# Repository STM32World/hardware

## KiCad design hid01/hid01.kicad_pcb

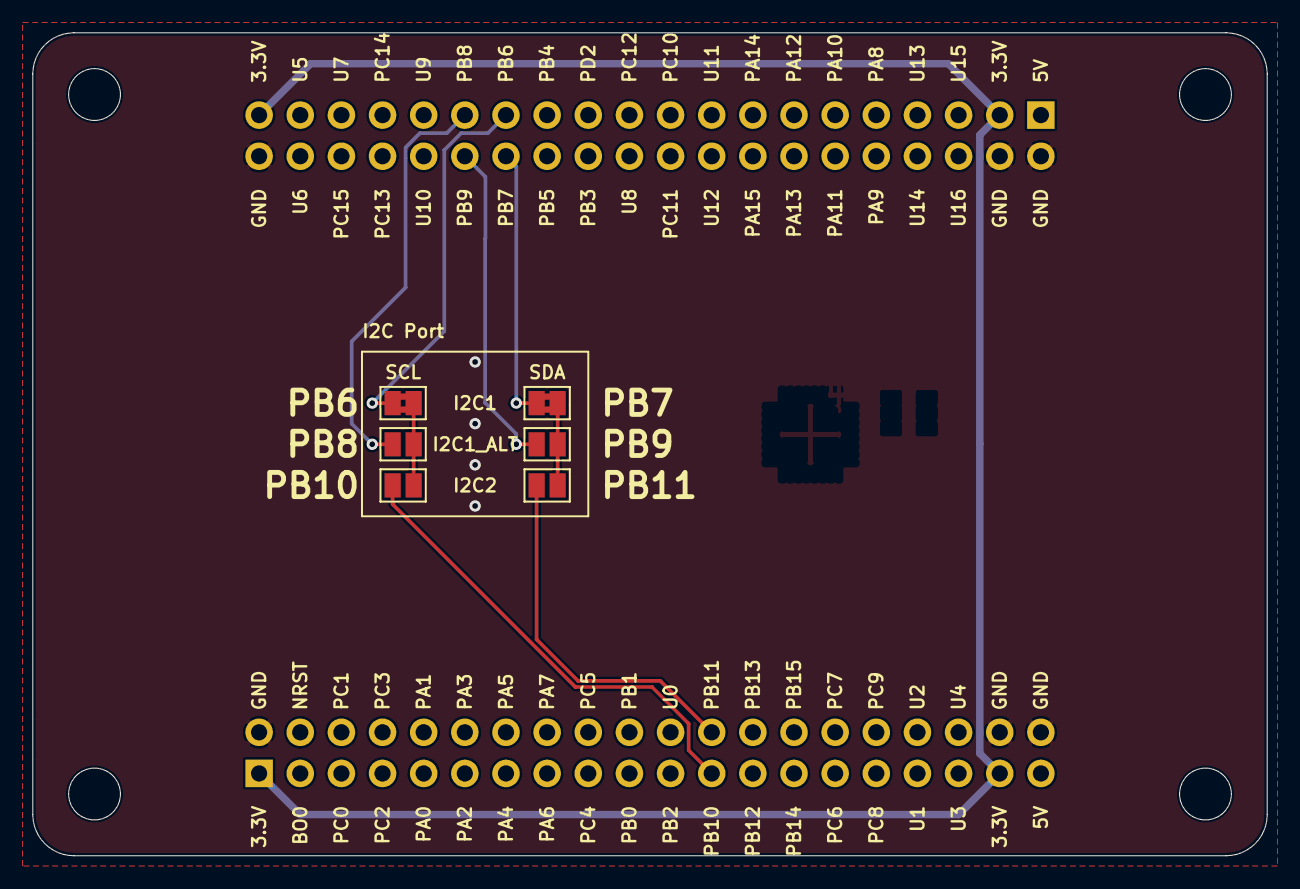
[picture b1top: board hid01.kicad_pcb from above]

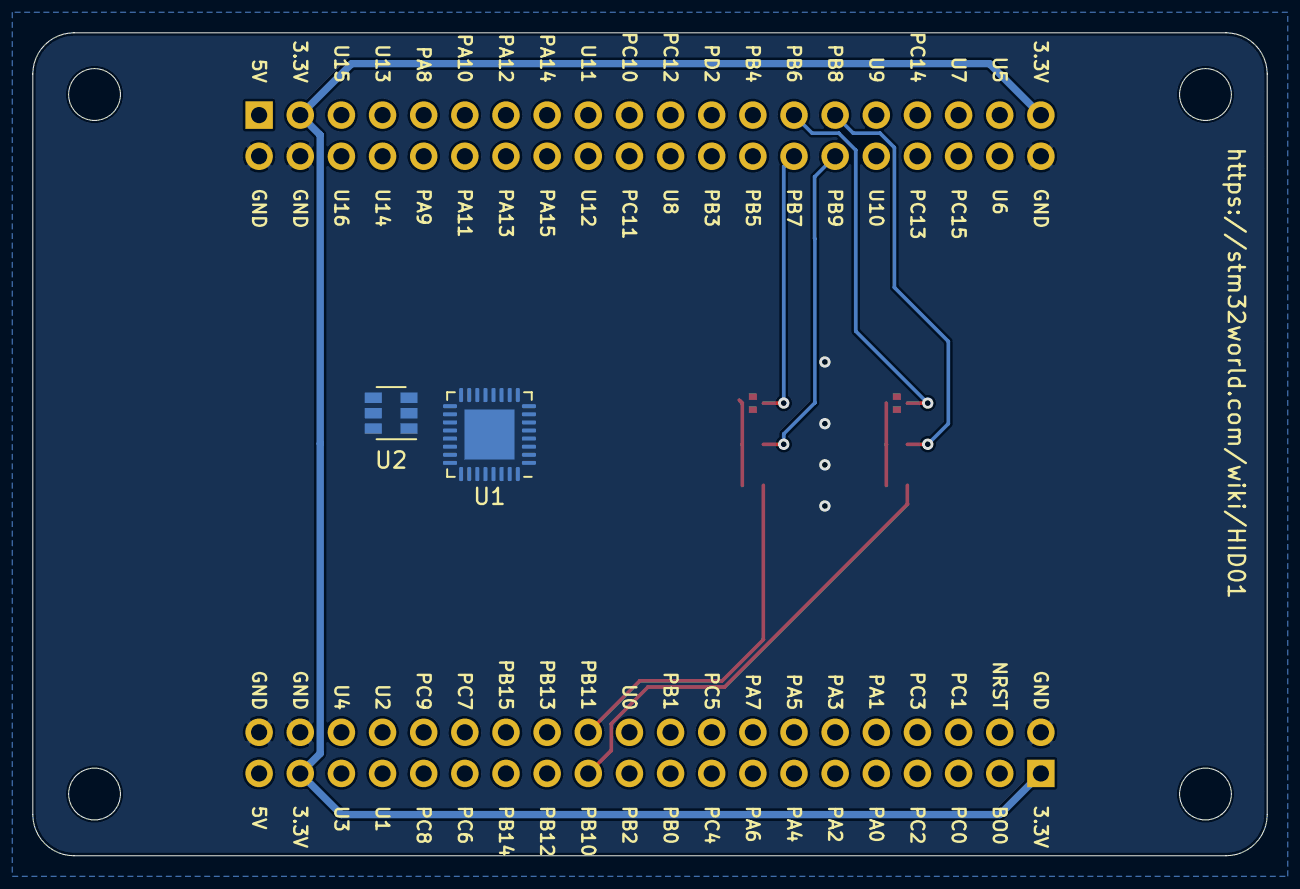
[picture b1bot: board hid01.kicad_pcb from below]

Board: 2 copper layers, 76.2 x 50.8 mm, 9 parts (2 on the bottom side), 10 nets.

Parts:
J1: STM32WORLD_BASE
JP1, JP3: SolderJumper-2_P1.3mm_Bridged2Bar_Pad1.0x1.5mm
JP2, JP4, JP7, JP8: SolderJumper-2_P1.3mm_Open_Pad1.0x1.5mm
U1: TCA6424ARGJR; QFN-32-1EP_5x5mm_P0.5mm_EP3.1x3.1mm
U2: TTP223E-HA6; SOT-23-6

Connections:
+3V3: J1.1, J1.37, J1.43, J1.79, U1.27, U1.28, U1.31
GND: J1.2, J1.38, J1.40, J1.42, J1.44, J1.80, U1.25, U1.26, U1.33
I2C1_SCL: J1.67, JP1.1
I2C1_SCL_ALT: J1.69, JP2.1
I2C1_SDA: J1.68, JP3.1
I2C1_SDA_ALT: J1.70, JP4.1
I2C2_SCL: J1.23, JP7.1
I2C2_SDA: J1.24, JP8.1
SCL: JP1.2, JP2.2, JP7.2, U1.29
SDA: JP3.2, JP4.2, JP8.2, U1.30

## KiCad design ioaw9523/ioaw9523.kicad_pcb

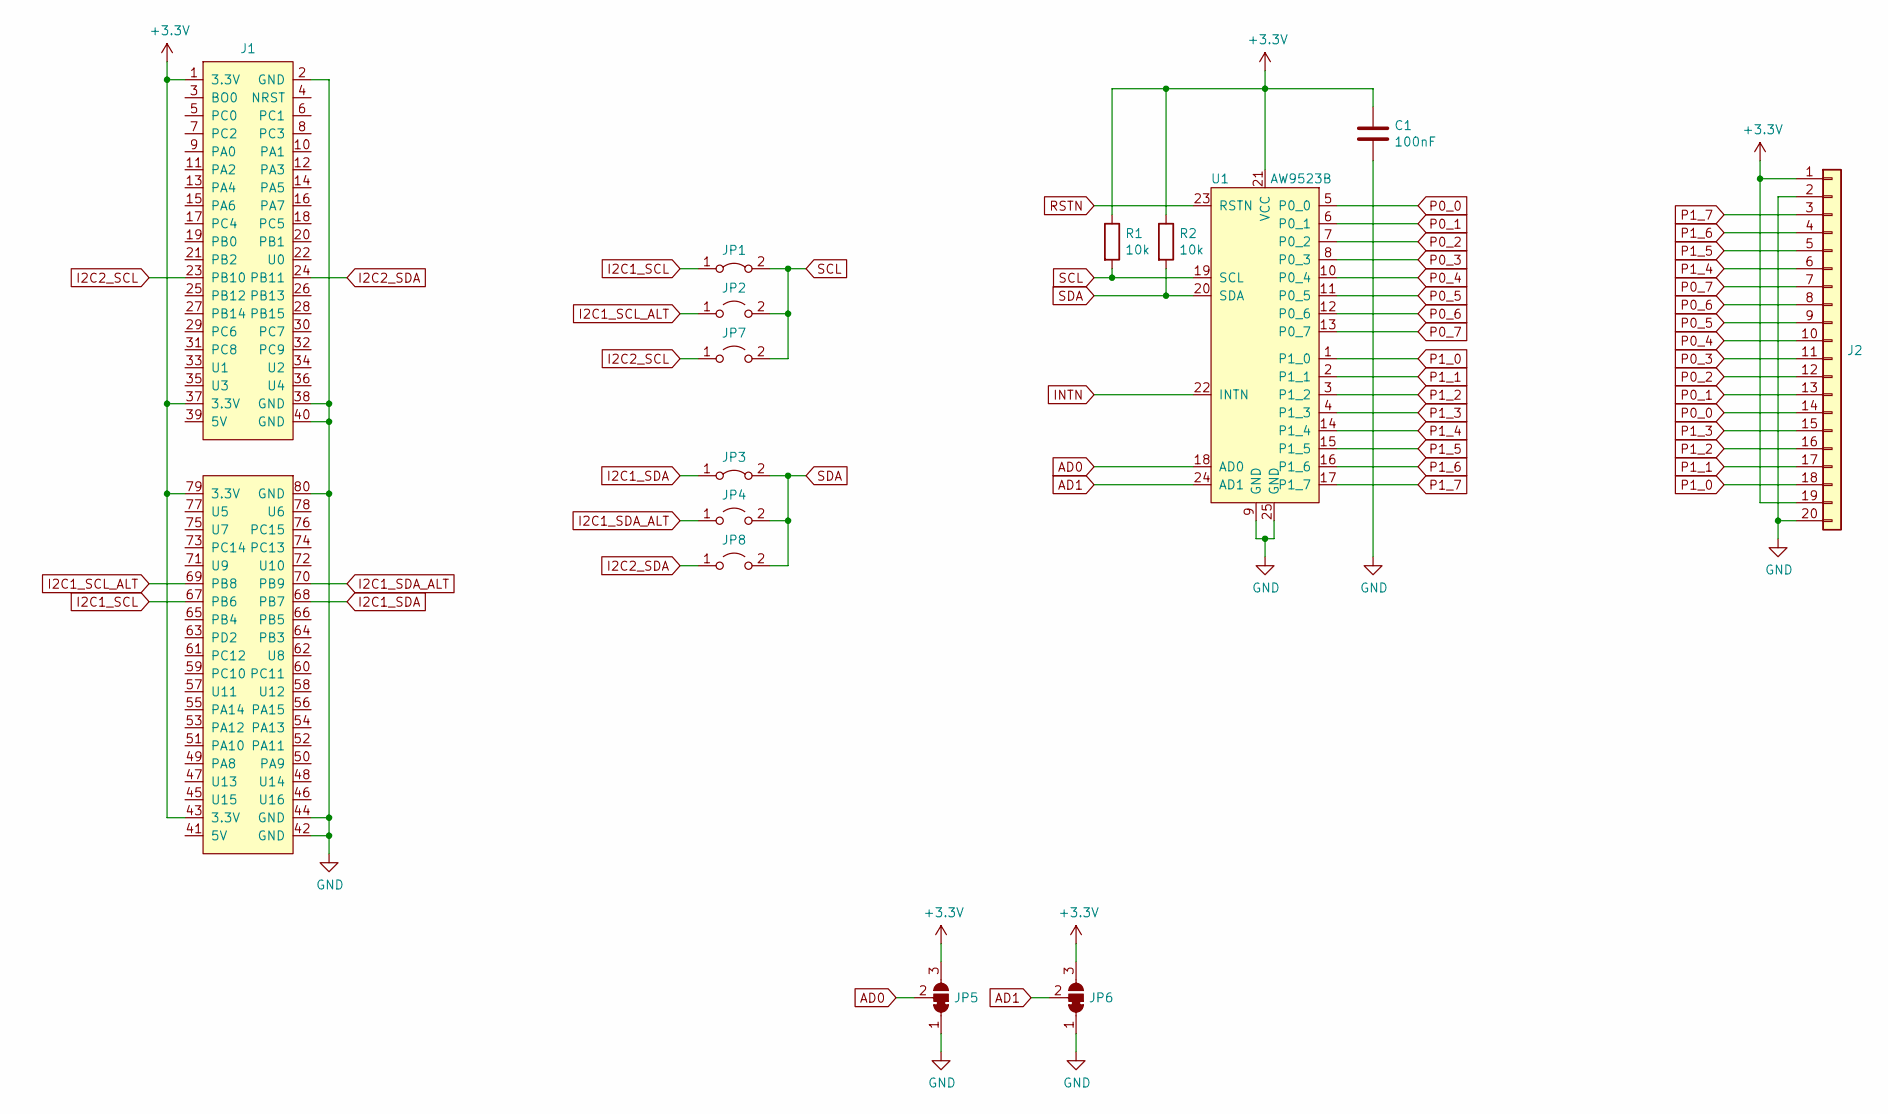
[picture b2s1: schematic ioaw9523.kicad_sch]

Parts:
C1: C_100NF_0603; C_0603_1608Metric; LCSC C14663
J1: STM32WORLD_BASE
J2: PinHeader_2x10_P2.54mm_Horizontal
JP1, JP3: SolderJumper-2_P1.3mm_Bridged2Bar_Pad1.0x1.5mm
JP2, JP4, JP7, JP8: SolderJumper-2_P1.3mm_Open_Pad1.0x1.5mm
JP5, JP6: SolderJumper-3_P1.3mm_Bridged12_Pad1.0x1.5mm
R1, R2: R_10K_0603; R_0603_1608Metric; LCSC C25804
U1: AW9523B; TQFN-24-1EP_4x4mm_P0.5mm_EP2.8x2.8mm_PullBack; LCSC C148077

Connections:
+3V3: C1.1, J1.1 (3.3V), J1.37 (3.3V), J1.43 (3.3V), J1.79 (3.3V), J2.1, J2.19, JP5.3 (B), JP6.3 (B), R1.1, R2.1, U1.21 (VCC)
AD0: JP5.2 (C), U1.18 (AD0)
AD1: JP6.2 (C), U1.24 (AD1)
GND: C1.2, J1.2 (GND), J1.38 (GND), J1.40 (GND), J1.42 (GND), J1.44 (GND), J1.80 (GND), J2.2, J2.20, JP5.1 (A), JP6.1 (A), U1.9 (GND), U1.25 (GND)
I2C1_SCL: J1.67 (PB6), JP1.1 (A)
I2C1_SCL_ALT: J1.69 (PB8), JP2.1 (A)
I2C1_SDA: J1.68 (PB7), JP3.1 (A)
I2C1_SDA_ALT: J1.70 (PB9), JP4.1 (A)
I2C2_SCL: J1.23 (PB10), JP7.1 (A)
I2C2_SDA: J1.24 (PB11), JP8.1 (A)
INTN: U1.22 (INTN)
P0_0: J2.14, U1.5 (P0_0)
P0_1: J2.13, U1.6 (P0_1)
P0_2: J2.12, U1.7 (P0_2)
P0_3: J2.11, U1.8 (P0_3)
P0_4: J2.10, U1.10 (P0_4)
P0_5: J2.9, U1.11 (P0_5)
P0_6: J2.8, U1.12 (P0_6)
P0_7: J2.7, U1.13 (P0_7)
P1_0: J2.18, U1.1 (P1_0)
P1_1: J2.17, U1.2 (P1_1)
P1_2: J2.16, U1.3 (P1_2)
P1_3: J2.15, U1.4 (P1_3)
P1_4: J2.6, U1.14 (P1_4)
P1_5: J2.5, U1.15 (P1_5)
P1_6: J2.4, U1.16 (P1_6)
P1_7: J2.3, U1.17 (P1_7)
RSTN: U1.23 (RSTN)
SCL: JP1.2 (B), JP2.2 (B), JP7.2 (B), R1.2, U1.19 (SCL)
SDA: JP3.2 (B), JP4.2 (B), JP8.2 (B), R2.2, U1.20 (SDA)

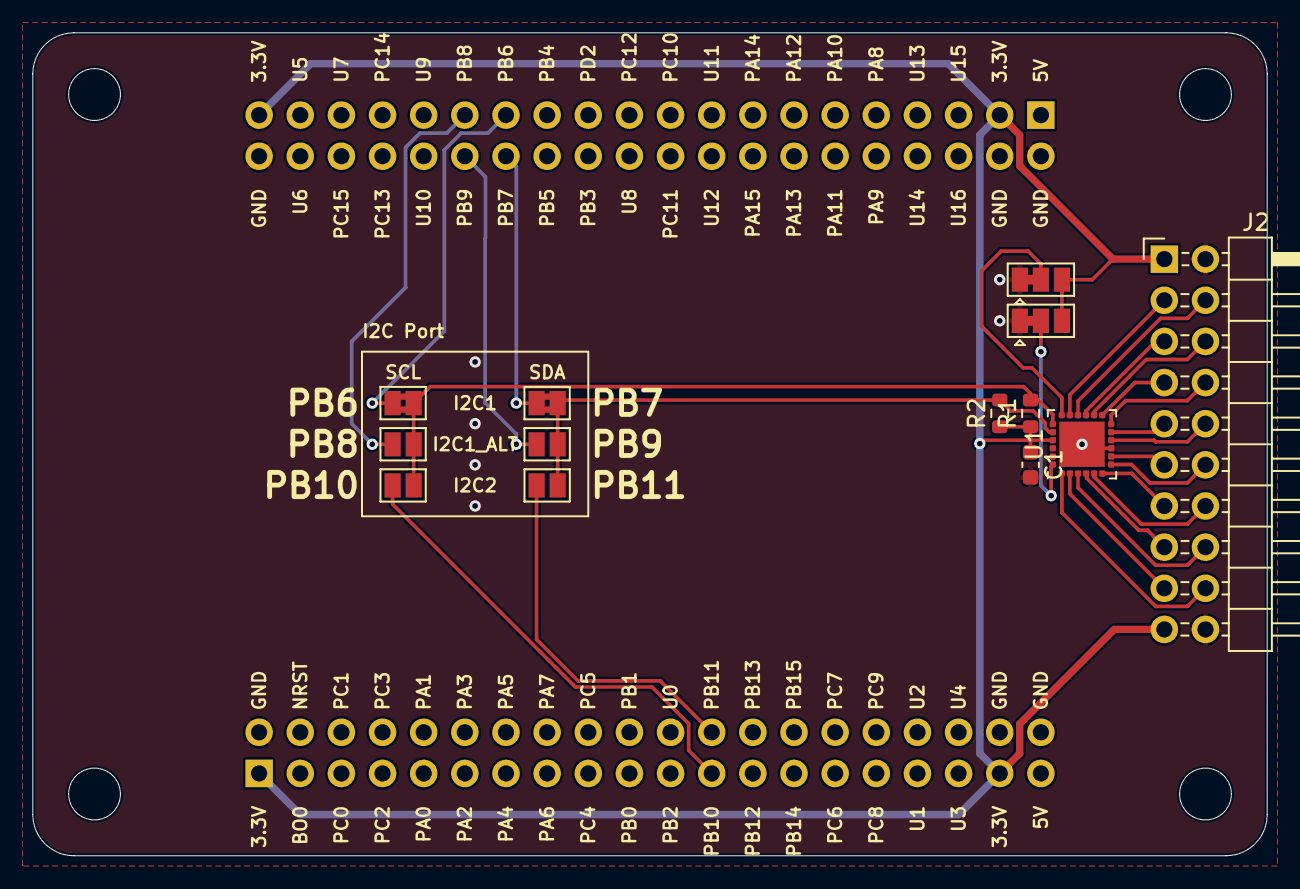
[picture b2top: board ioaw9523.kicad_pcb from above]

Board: 2 copper layers, 76.2 x 50.8 mm, 14 parts (0 on the bottom side), 28 nets.

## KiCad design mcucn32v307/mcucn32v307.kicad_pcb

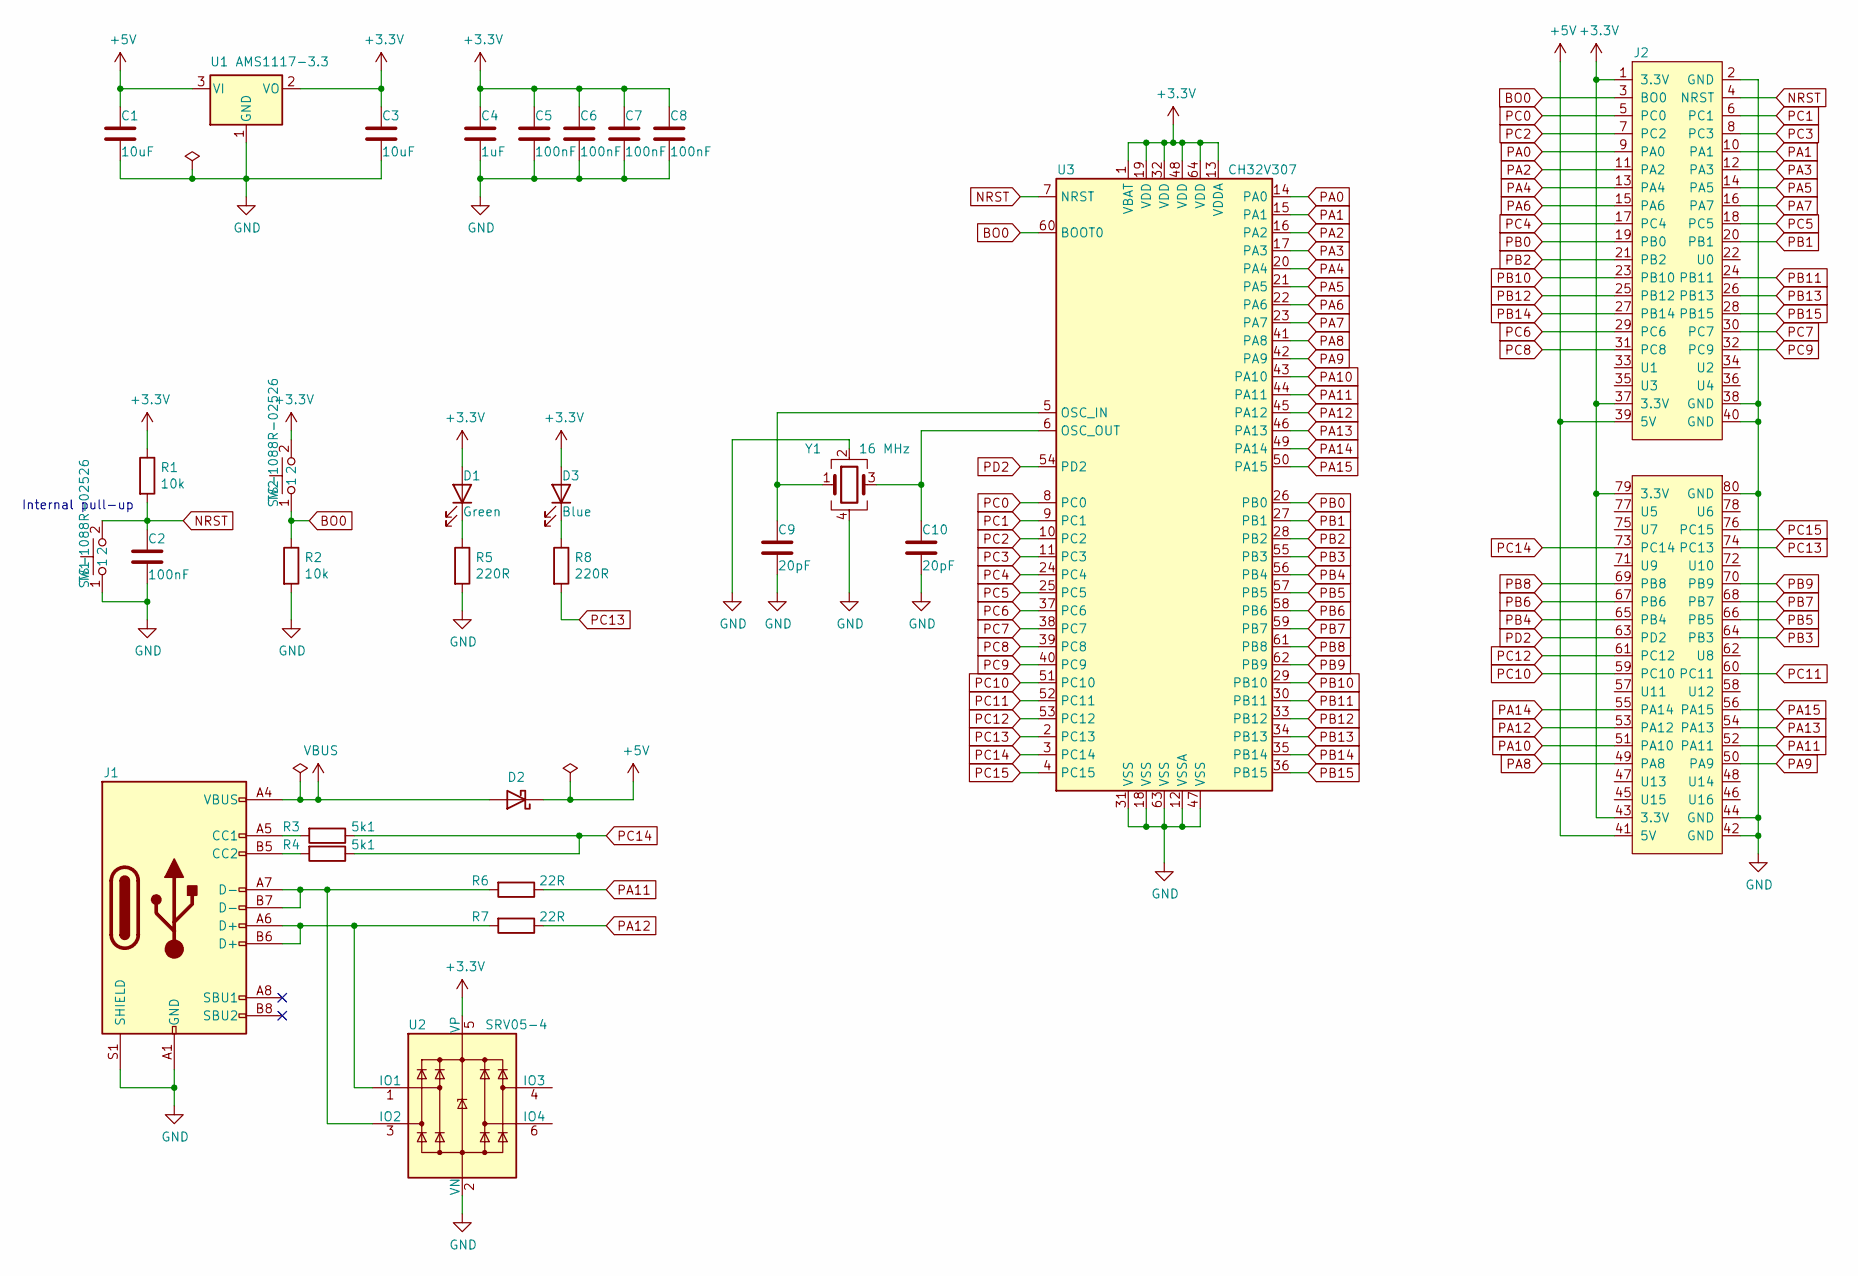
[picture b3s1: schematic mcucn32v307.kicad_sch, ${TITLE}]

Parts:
C1, C3: C_10UF_0805; C_0805_2012Metric; LCSC C15850
C2, C5, C6, C7, C8: C_100NF_0603; C_0603_1608Metric; LCSC C14663
C4: C_1UF_0603; C_0603_1608Metric; LCSC C15849
C9, C10: C_20PF_0603; C_0603_1608Metric; LCSC C1648
D1: LED_GREEN_0603; LED_0603_1608Metric; LCSC C72043
D2: LCSC C8598
D3: LED_BLUE_0603; LED_0603_1608Metric; LCSC C72041
J1: USB_C_Receptacle_USB2.0; USB_C_Receptacle_HRO_TYPE-C-31-M-12; LCSC C165948
J2: STM32WORLD_BASE
R1, R2: R_10K_0603; R_0603_1608Metric; LCSC C25804
R3, R4: R_5.1K_0603; R_0603_1608Metric; LCSC C23186
R5, R8: R_220_0603; R_0603_1608Metric; LCSC C22962
R6, R7: R_22_0603; R_0603_1608Metric; LCSC C23345
SW1, SW2: TS-1088R-02526; LCSC C455281
U1: AMS1117-3.3; SOT-223-3_TabPin2; LCSC C6186
U2: SRV05-4; SOT-23-6; LCSC C85364
U3: CH32V307; LQFP-64_10x10mm_P0.5mm; LCSC C2988083
Y1: X_16MHZ; Crystal_SMD_3225-4Pin_3.2x2.5mm; LCSC C13738

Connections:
+3V3: C3.1, C4.1, C5.1, C6.1, C7.1, C8.1, D1.2 (A), D3.2 (A), J2.1 (3.3V), J2.37 (3.3V), J2.43 (3.3V), J2.79 (3.3V), R1.1, SW2.2, U1.2 (VO), U2.5 (VP), U3.1 (VBAT), U3.13 (VDDA), U3.19 (VDD), U3.32 (VDD), U3.48 (VDD), U3.64 (VDD)
+5V: C1.1, D2.1 (K), J2.39 (5V), J2.41 (5V), U1.3 (VI)
BO0: J2.3 (BO0), R2.1, SW2.1, U3.60 (BOOT0)
GND: C1.2, C2.2, C3.2, C4.2, C5.2, C6.2, C7.2, C8.2, C9.2, C10.2, J1.A1 (GND), J1.A12 (GND), J1.B1 (GND), J1.B12 (GND), J1.S1 (SHIELD), J2.2 (GND), J2.38 (GND), J2.40 (GND), J2.42 (GND), J2.44 (GND), J2.80 (GND), R2.2, R5.2, SW1.1, U1.1 (GND), U2.2 (VN), U3.12 (VSSA), U3.18 (VSS), U3.31 (VSS), U3.47 (VSS), U3.63 (VSS), Y1.2, Y1.4
NRST: C2.1, J2.4 (NRST), R1.2, SW1.2, U3.7 (NRST)
unnamed: C9.1, U3.5 (OSC_IN), Y1.1
unnamed: C10.1, U3.6 (OSC_OUT), Y1.3
unnamed: D1.1 (K), R5.1
unnamed: D3.1 (K), R8.1
unnamed: J1.A5 (CC1), R3.2
unnamed: J1.A6 (D+), J1.B6 (D+), R7.2, U2.1 (IO1)
unnamed: J1.A7 (D-), J1.B7 (D-), R6.2, U2.3 (IO2)
unnamed: J1.B5 (CC2), R4.2
PA0: J2.9 (PA0), U3.14 (PA0)
PA1: J2.10 (PA1), U3.15 (PA1)
PA2: J2.11 (PA2), U3.16 (PA2)
PA3: J2.12 (PA3), U3.17 (PA3)
PA4: J2.13 (PA4), U3.20 (PA4)
PA5: J2.14 (PA5), U3.21 (PA5)
PA6: J2.15 (PA6), U3.22 (PA6)
PA7: J2.16 (PA7), U3.23 (PA7)
PA8: J2.49 (PA8), U3.41 (PA8)
PA9: J2.50 (PA9), U3.42 (PA9)
PA10: J2.51 (PA10), U3.43 (PA10)
PA11: J2.52 (PA11), R6.1, U3.44 (PA11)
PA12: J2.53 (PA12), R7.1, U3.45 (PA12)
PA13: J2.54 (PA13), U3.46 (PA13)
PA14: J2.55 (PA14), U3.49 (PA14)
PA15: J2.56 (PA15), U3.50 (PA15)
PB0: J2.19 (PB0), U3.26 (PB0)
PB1: J2.20 (PB1), U3.27 (PB1)
PB2: J2.21 (PB2), U3.28 (PB2)
PB3: J2.64 (PB3), U3.55 (PB3)
PB4: J2.65 (PB4), U3.56 (PB4)
PB5: J2.66 (PB5), U3.57 (PB5)
PB6: J2.67 (PB6), U3.58 (PB6)
PB7: J2.68 (PB7), U3.59 (PB7)
PB8: J2.69 (PB8), U3.61 (PB8)
PB9: J2.70 (PB9), U3.62 (PB9)
PB10: J2.23 (PB10), U3.29 (PB10)
PB11: J2.24 (PB11), U3.30 (PB11)
PB12: J2.25 (PB12), U3.33 (PB12)
PB13: J2.26 (PB13), U3.34 (PB13)
PB14: J2.27 (PB14), U3.35 (PB14)
PB15: J2.28 (PB15), U3.36 (PB15)
PC0: J2.5 (PC0), U3.8 (PC0)
PC1: J2.6 (PC1), U3.9 (PC1)
PC2: J2.7 (PC2), U3.10 (PC2)
PC3: J2.8 (PC3), U3.11 (PC3)
PC4: J2.17 (PC4), U3.24 (PC4)
PC5: J2.18 (PC5), U3.25 (PC5)
PC6: J2.29 (PC6), U3.37 (PC6)
PC7: J2.30 (PC7), U3.38 (PC7)
PC8: J2.31 (PC8), U3.39 (PC8)
PC9: J2.32 (PC9), U3.40 (PC9)
PC10: J2.59 (PC10), U3.51 (PC10)
PC11: J2.60 (PC11), U3.52 (PC11)
PC12: J2.61 (PC12), U3.53 (PC12)
PC13: J2.74 (PC13), R8.2, U3.2 (PC13)
PC14: J2.73 (PC14), R3.1, R4.1, U3.3 (PC14)
PC15: J2.76 (PC15), U3.4 (PC15)
PD2: J2.63 (PD2), U3.54 (PD2)
VBUS: D2.2 (A), J1.A4 (VBUS), J1.A9 (VBUS), J1.B4 (VBUS), J1.B9 (VBUS)

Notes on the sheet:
Internal pull-up

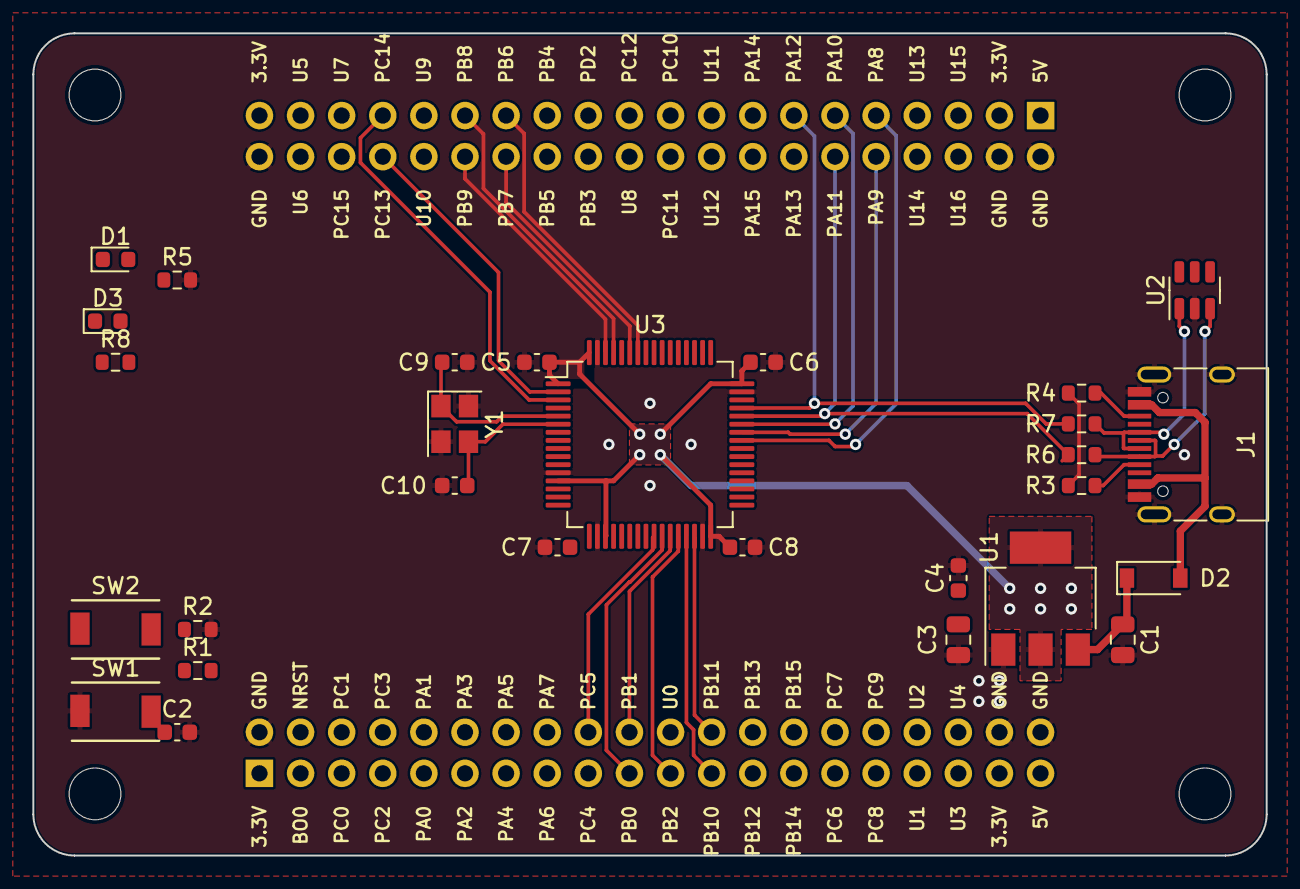
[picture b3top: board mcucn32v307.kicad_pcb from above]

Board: 2 copper layers, 76.2 x 50.8 mm, 29 parts (0 on the bottom side), 63 nets.

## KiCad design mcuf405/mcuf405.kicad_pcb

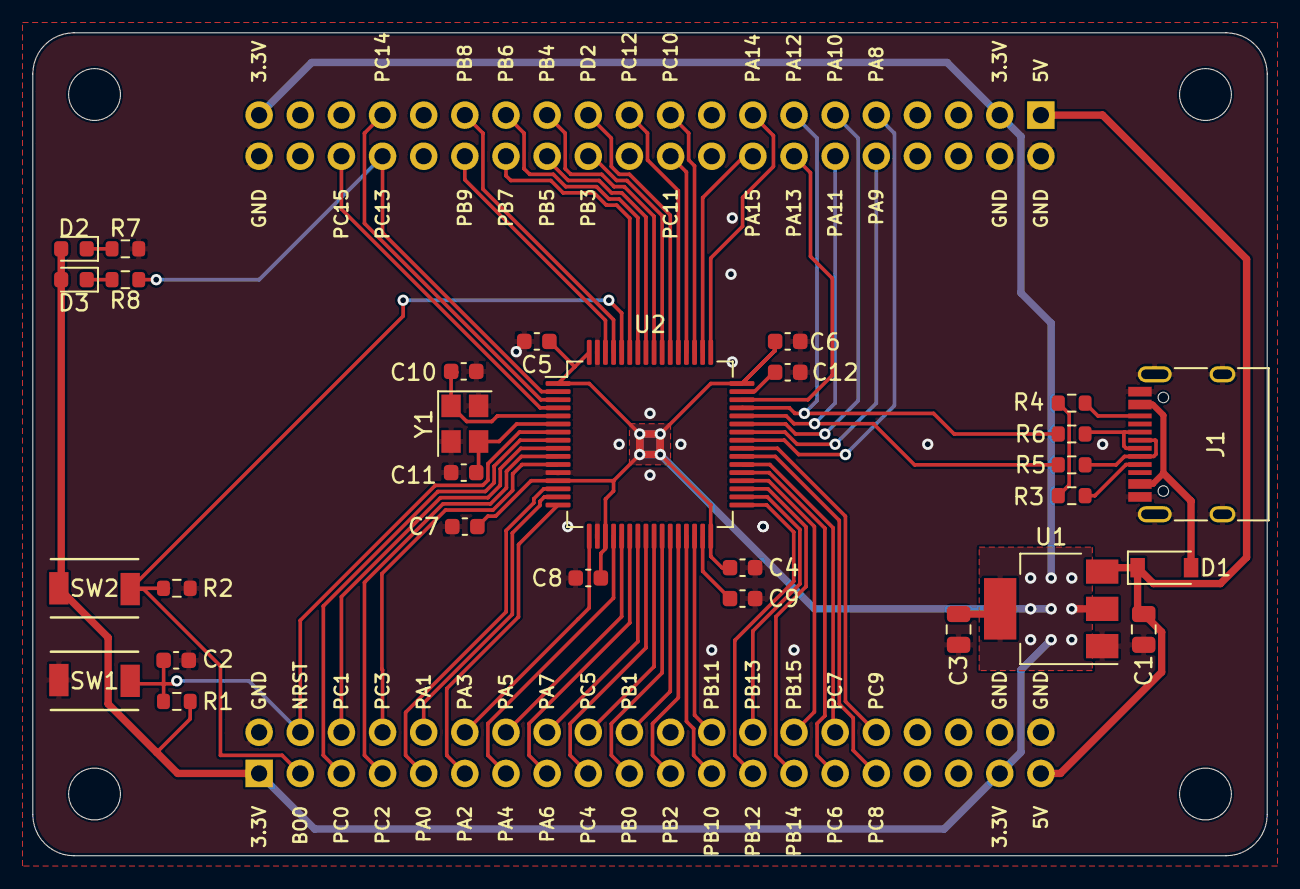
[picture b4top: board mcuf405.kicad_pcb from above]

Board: 2 copper layers, 76.2 x 50.8 mm, 30 parts (0 on the bottom side), 66 nets.

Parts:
C1, C3: C_10UF_0805; C_0805_2012Metric
C2, C5, C6, C7, C8: C_100NF_0603; C_0603_1608Metric
C4: C_1UF_0603; C_0603_1608Metric
C9, C12: C_2.2UF_0603; C_0603_1608Metric
C10, C11: C_20PF_0603; C_0603_1608Metric
D1: D_SOD-123
D2: LED_GREEN_0603; LED_0603_1608Metric
D3: LED_BLUE_0603; LED_0603_1608Metric
J1: USB_C_Receptacle_HRO_TYPE-C-31-M-12
J2: STM32WORLD_BASE
R1, R2: R_10K_0603; R_0603_1608Metric
R3, R4: R_5.1K_0603; R_0603_1608Metric
R5, R6: R_22_0603; R_0603_1608Metric
R7, R8: R_220_0603; R_0603_1608Metric
SW1, SW2: TS-1088R-02526
U1: AMS1117-3.3; SOT-223-3_TabPin2
U2: STM32F405RGTx; LQFP-64_10x10mm_P0.5mm
Y1: X_16MHZ; Crystal_SMD_3225-4Pin_3.2x2.5mm

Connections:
+3V3: C3.1, C4.1, C5.1, C6.1, C7.1, C8.1, D2.2, D3.2, J2.1, J2.37, J2.43, J2.79, R1.1, SW2.2, U1.2, U2.1, U2.13, U2.19, U2.32, U2.48, U2.64
+5V: C1.1, D1.1, J2.39, J2.41, U1.3
BO0: J2.3, R2.1, SW2.1, U2.60
GND: C1.2, C2.2, C3.2, C4.2, C5.2, C6.2, C7.2, C8.2, C9.2, C10.2, C11.2, C12.2, J1.A1, J1.A12, J1.B1, J1.B12, J1.S1, J2.2, J2.38, J2.40, J2.42, J2.44, J2.80, R2.2, R7.2, SW1.1, U1.1, U2.12, U2.18, U2.63, Y1.2, Y1.4
NRST: C2.1, J2.4, R1.2, SW1.2, U2.7
unnamed: C9.1, U2.31
unnamed: C10.1, U2.5, Y1.1
unnamed: C11.1, U2.6, Y1.3
unnamed: C12.1, U2.47
unnamed: D2.1, R7.1
unnamed: D3.1, R8.1
unnamed: J1.A5, R3.2
unnamed: J1.A6, J1.B6, R6.2
unnamed: J1.A7, J1.B7, R5.2
unnamed: J1.B5, R4.2
PA0: J2.9, U2.14
PA1: J2.10, U2.15
PA2: J2.11, U2.16
PA3: J2.12, U2.17
PA4: J2.13, U2.20
PA5: J2.14, U2.21
PA6: J2.15, U2.22
PA7: J2.16, U2.23
PA8: J2.49, U2.41
PA9: J2.50, U2.42
PA10: J2.51, U2.43
PA11: J2.52, R5.1, U2.44
PA12: J2.53, R6.1, U2.45
PA13: J2.54, U2.46
PA14: J2.55, U2.49
PA15: J2.56, U2.50
PB0: J2.19, U2.26
PB1: J2.20, U2.27
PB2: J2.21, U2.28
PB3: J2.64, U2.55
PB4: J2.65, U2.56
PB5: J2.66, U2.57
PB6: J2.67, U2.58
PB7: J2.68, U2.59
PB8: J2.69, U2.61
PB9: J2.70, U2.62
PB10: J2.23, U2.29
PB11: J2.24, U2.30
PB12: J2.25, U2.33
PB13: J2.26, U2.34
PB14: J2.27, U2.35
PB15: J2.28, U2.36
PC0: J2.5, U2.8
PC1: J2.6, U2.9
PC2: J2.7, U2.10
PC3: J2.8, U2.11
PC4: J2.17, U2.24
PC5: J2.18, U2.25
PC6: J2.29, U2.37
PC7: J2.30, U2.38
PC8: J2.31, U2.39
PC9: J2.32, U2.40
PC10: J2.59, U2.51
PC11: J2.60, U2.52
PC12: J2.61, U2.53
PC13: J2.74, R8.2, U2.2
PC14: J2.73, U2.3
PC15: J2.76, U2.4
PD2: J2.63, U2.54
UCC: R3.1, R4.1
VBUS: D1.2, J1.A4, J1.A9, J1.B4, J1.B9

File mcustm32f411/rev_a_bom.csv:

Comment,Designator,Footprint,Display,LCSC
"C_10UF_0805","C1,C3","Capacitor_SMD:C_0805_2012Metric","10uF","C15850"
"C_20PF_0603","C10,C11","Capacitor_SMD:C_0603_1608Metric","20pF","C1648"
"C_100NF_0603","C2,C5,C6,C7,C8","Capacitor_SMD:C_0603_1608Metric","100nF","C14663"
"C_1UF_0603","C4","Capacitor_SMD:C_0603_1608Metric","1uF","C15849"
"C_4.7UF_0603","C9","Capacitor_SMD:C_0603_1608Metric","4.7uF","C19666"
"~","D1","Diode_SMD:D_SOD-123","","C8598"
"LED_GREEN_0603","D2","LED_SMD:LED_0603_1608Metric","Green","C72043"
"LED_BLUE_0603","D3","LED_SMD:LED_0603_1608Metric","Blue","C72041"
"~","J1","stm32world:USB_C_Receptacle_HRO_TYPE-C-31-M-12","","C165948"
"STM32WORLD_BASE","J2","stm32world:STM32WORLD_BASE"
"R_10K_0603","R1,R2","Resistor_SMD:R_0603_1608Metric","10k","C25804"
"R_5.1K_0603","R3,R4","Resistor_SMD:R_0603_1608Metric","5.1k","C23186"
"R_22_0603","R5,R6","Resistor_SMD:R_0603_1608Metric","22R","C23345"
"R_220_0603","R7,R8","Resistor_SMD:R_0603_1608Metric","220R","C22962"
"~","SW1,SW2","stm32world:TS-1088R-02526","","C455281"
"AMS1117-3.3","U1","Package_TO_SOT_SMD:SOT-223-3_TabPin2","","C6186"
"STM32F411CEUx","U2","Package_DFN_QFN:QFN-48-1EP_7x7mm_P0.5mm_EP5.6x5.6mm"
"SRV05-4","U3","Package_TO_SOT_SMD:SOT-23-6","","C85364"
"X_16MHZ","Y1","Crystal:Crystal_SMD_3225-4Pin_3.2x2.5mm","16 MHz","C13738"
